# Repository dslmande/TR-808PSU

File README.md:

# TR-808PSU

> ## ⚠️ UNTESTED
>
> **This board has not been manufactured, assembled or tested.** It has not been checked
> against the real unit, and it has not been tested against any safety standard. The design
> is a copy of a historical (1984–86) circuit board. It is connected to **mains voltage
> (230 V, or 110 V for the second variant)**, which can kill. Use at your own risk, and only if you know what you are doing.
> Dimensions are derived from a scan (±3 %), see [VERIFICATION.md](VERIFICATION.md).

KiCad rebuild of the power supply board **PS3116 (PCB 291-405A)** of the Roland TR-808:
schematic redrawn from the 1981 service manual, board with outline, holes, terminals and
component positions taken from the original component layout. Two variants of the same board:

| Variant | Original board | Mains | Transformer | Files |
|---|---|---|---|---|
| **230 V** | PS3116-054 | 220/240 V | N-219D | `TR-808PSU_Rev0.5*` |
| **110 V** | PS3116-051 | 100/117 V (built for 110 V, 117 V tap) | N-218C | `TR-808PSU_Rev0.5-110V*` |

Both use the same copper; they differ in parts (fuses, transformer, switch, C1) and in the
silkscreen mark (`PS3116-054  230V` / `PS3116-051  110V`), so the boards cannot be mixed up.
Current version: **Rev0.5**.

| Version | Contents |
|---|---|
| [Rev0.1](https://github.com/dslmande/TR-808PSU/releases/tag/Rev0.1) | historical 1:1 copy of the 1984–86 original; switched mains conductors SW_A/SW_B 3.75 mm apart |
| [Rev0.2](https://github.com/dslmande/TR-808PSU/releases/tag/Rev0.2) | as Rev0.1, but SW_B moved away on the mains side: SW_A/SW_B at least 5.67 mm apart |
| [Rev0.3](https://github.com/dslmande/TR-808PSU/releases/tag/Rev0.3) | as Rev0.2, but the 230 V primary side (terminals 1–9: mains, switch, transformer input) uses **RM5.0 screw terminals** (Phoenix MKDS 1,5) instead of solder lugs; terminals 10–22 (low voltage) stay solder lugs |
| [Rev0.4](https://github.com/dslmande/TR-808PSU/releases/tag/Rev0.4) / [Rev0.4-110V](https://github.com/dslmande/TR-808PSU/releases/tag/Rev0.4-110V) | as Rev0.3, but all board corners rounded to R5 (house rule), voltage mark on the silkscreen; the 110 V variant is new (fuses 0.5 A, transformer N-218C) |
| **Rev0.5** / **Rev0.5-110V** (current) | as Rev0.4, but the voltage mark moved to the free area below the fuse holders (it touched the F4 outline). Two releases: 230 V and 110 V |

## Pictures (230 V)

### 110 V variant

More (230 V; for 110 V use the `Rev0.5-110V` files, [BOM-110V.md](BOM-110V.md)): [schematic (PDF)](psu/TR-808PSU_Rev0.5_schaltplan.pdf) · [bill of materials](BOM.md) ([CSV](psu/TR-808PSU_Rev0.5_bom.csv)) · [1:1 printout (A4)](psu/TR-808PSU_Rev0.5_ausdruck_1zu1.pdf) · [Gerber (zip)](psu/TR-808PSU_Rev0.5_gerber.zip) · [assembly drawing (PDF)](psu/TR-808PSU_Rev0.5_assembly.pdf) · [original copper vs. tracks](psu/TR-808PSU_Rev0.5_ueberlagerung.png) · [verification](VERIFICATION.md) · [releases](https://github.com/dslmande/TR-808PSU/releases)

## Files

| File | Contents |
|---|---|
| [ORIGINAL.md](ORIGINAL.md) | source, manual pages, variants, circuit description, open points |
| [VERIFICATION.md](VERIFICATION.md) | standards context (DIN EN IEC 62368-1, IEC 60664-1), verification, validation, findings, risks |
| [BOM.md](BOM.md) / [BOM-110V.md](BOM-110V.md), `psu/TR-808PSU_Rev0.5_bom.csv` | bill of materials (readable, with function and original parts; CSV) |
| `psu/TR-808PSU_Rev0.5.kicad_pro` / `.kicad_sch` / `.kicad_pcb` (and `…Rev0.5-110V…`) | KiCad project |
| `psu/TR-808PSU_Rev0.5_schaltplan.pdf` | schematic plot |
| `psu/gerber_TR-808PSU_Rev0.5/`, `psu/TR-808PSU_Rev0.5_gerber.zip` | Gerber, drill data, position file |
| `psu/TR-808PSU_Rev0.5_ausdruck_1zu1.pdf` | 1:1 printout on A4 landscape: component side, solder side, drill template (print at 100 %, check the measuring bar) |
| `psu/TR-808PSU_Rev0.5_3d_oben.png`, `_3d_schraeg.png` | 3D views (KiCad ray tracing; own models for fuse holders and terminal lugs) |
| `psu/TR-808PSU_Rev0.5_pcb_top.pdf`, `_pcb_bottom.pdf`, `_assembly.pdf` | board plots |
| `psu/placement.json`, `psu/placement_scan.json` | component positions from the component layout, resp. aligned to the scan (mm) |
| `psu/kupfer.npz`, `psu/leitkarte.npz` | copper mask and net regions of the original (from the scan) |
| `psu/TR-808PSU_Rev0.5_ueberlagerung.png` | original copper against the tracks of this board |

File names with `schaltplan`, `ausdruck`, `kupfer` and `leitkarte` are German for schematic, printout, copper and guide map.

## What "1:1" means here

* **Circuit:** designators (C1–C16, R1–R7, D1–D4, F1–F4, Q1, Q2, IC1, IC2), values and
  terminal numbers 1–22 as in the original. The schematic is drawn like the original
  (mains and switch left, transformer, +5 V branch, ±15 V branch).
* **Board:** outline (from Rev0.5 with R5 corners instead of the sharp corners of the original), four mounting holes, six heat sink holes (one pair per regulator,
  21.3 mm apart, centred) and three M3 screw holes for the regulators, RM5 screw terminals
  (terminals 1–9), terminal pins (10–22), fuse clips and all components at the positions of
  the original, fine-tuned to the copper of the scan. The original is single
  sided with one wire jumper; this rebuild is two-layer.
* **Tracks: guided by the original, not copied one to one.** The copper of the original is
  extracted from the scan (halftone → mask → net regions) and used as a cost map by the
  router: original copper is cheap, everything else is expensive, the component side is
  almost blocked. The result is a DRC-clean board that follows the original where the scan
  allows. **37 % of the track length lies on original copper**, the rest is routed anew
  (wide tracks and smoothing move the paths away from the original);
  `psu/TR-808PSU_Rev0.5_ueberlagerung.png` shows the original copper (grey) and the tracks
  (red solder side, blue component side). Pure tracing without the router fails because of
  the scan quality (shorts between neighbouring tracks, pad positions only within ±0.3 mm).
* **Dimensions** are derived from the component layout (the manual has no scale), tolerance
  about ±3 %. Measure against a real board before manufacturing. Details and further open
  points in [ORIGINAL.md](ORIGINAL.md).

## Status (Rev0.5, 10 Oct 2026; both variants)

* **ERC:** 0 violations (`psu/TR-808PSU_Rev0.5-erc.rpt`).
* **DRC (clearance rule 0.25 mm):** 0 errors; warnings only (4 courtyard overlaps, 1
  silkscreen overlap, 7 footprint deviations from the library because of the polarity bars);
  0 unconnected items; schematic/board parity 0.
* **Mains against low voltage:** more than 8 mm copper to copper;
  between the mains conductors 4.0–5.67 mm, adjacent terminal poles 2.4 mm (RM5 pitch).
* **Netlist against the schematic:** read by hand from the schematic and checked against the
  plot; no independent comparison, see "Open" in [ORIGINAL.md](ORIGINAL.md).
* Track width 1.0 mm throughout; hairpins and stubs in pads are
  removed; smoothed (45°, arcs). No copper pours, as in the original. Five
  vias; most of the copper is on the solder side, about 440 mm of track on the component side
  (the original used the wire jumper J1 for this).
* **Silkscreen:** designators only (no values), terminal numbers 1–9 next to the screw
  terminals and P10–P22 on the pins, electrolytic polarity as a bar at the minus side as in
  the original, the four fuse holders F1–F4 on one line.
* **Not done:** assembly and measurement on the unit, manufacturing, any safety testing.

## Rebuilding

Schematic and layout were generated with a private tool chain that is not part of this
repo. The KiCad project in `psu/` is complete and needs only KiCad 9/10.

## License

Hardware files (KiCad project, Gerber, schematic, documents):
[CERN-OHL-W-2.0](LICENSE) (CERN Open Hardware Licence v2, weakly reciprocal). The licence
covers only this redrawing and layout, not Roland's original design or manual. Provided as is, without
warranty: see the disclaimer in the licence and the UNTESTED notice above.

## Source and rights

Circuit and dimensions come from the Roland TR-808 service manual (15 June 1981). The manual
itself and the data sheets are not part of this repo (copyright of Roland and the
manufacturers). This repo contains an own redrawing for repair and rebuild. "Roland" and
"TR-808" are trademarks of Roland Corporation; this project is not affiliated with Roland.

Data sheets used to check the pin assignments: 2SB596 (MOSPEC), 2SD880 (DC Components),
TA7179P and µA7805 (service manual, page 2).

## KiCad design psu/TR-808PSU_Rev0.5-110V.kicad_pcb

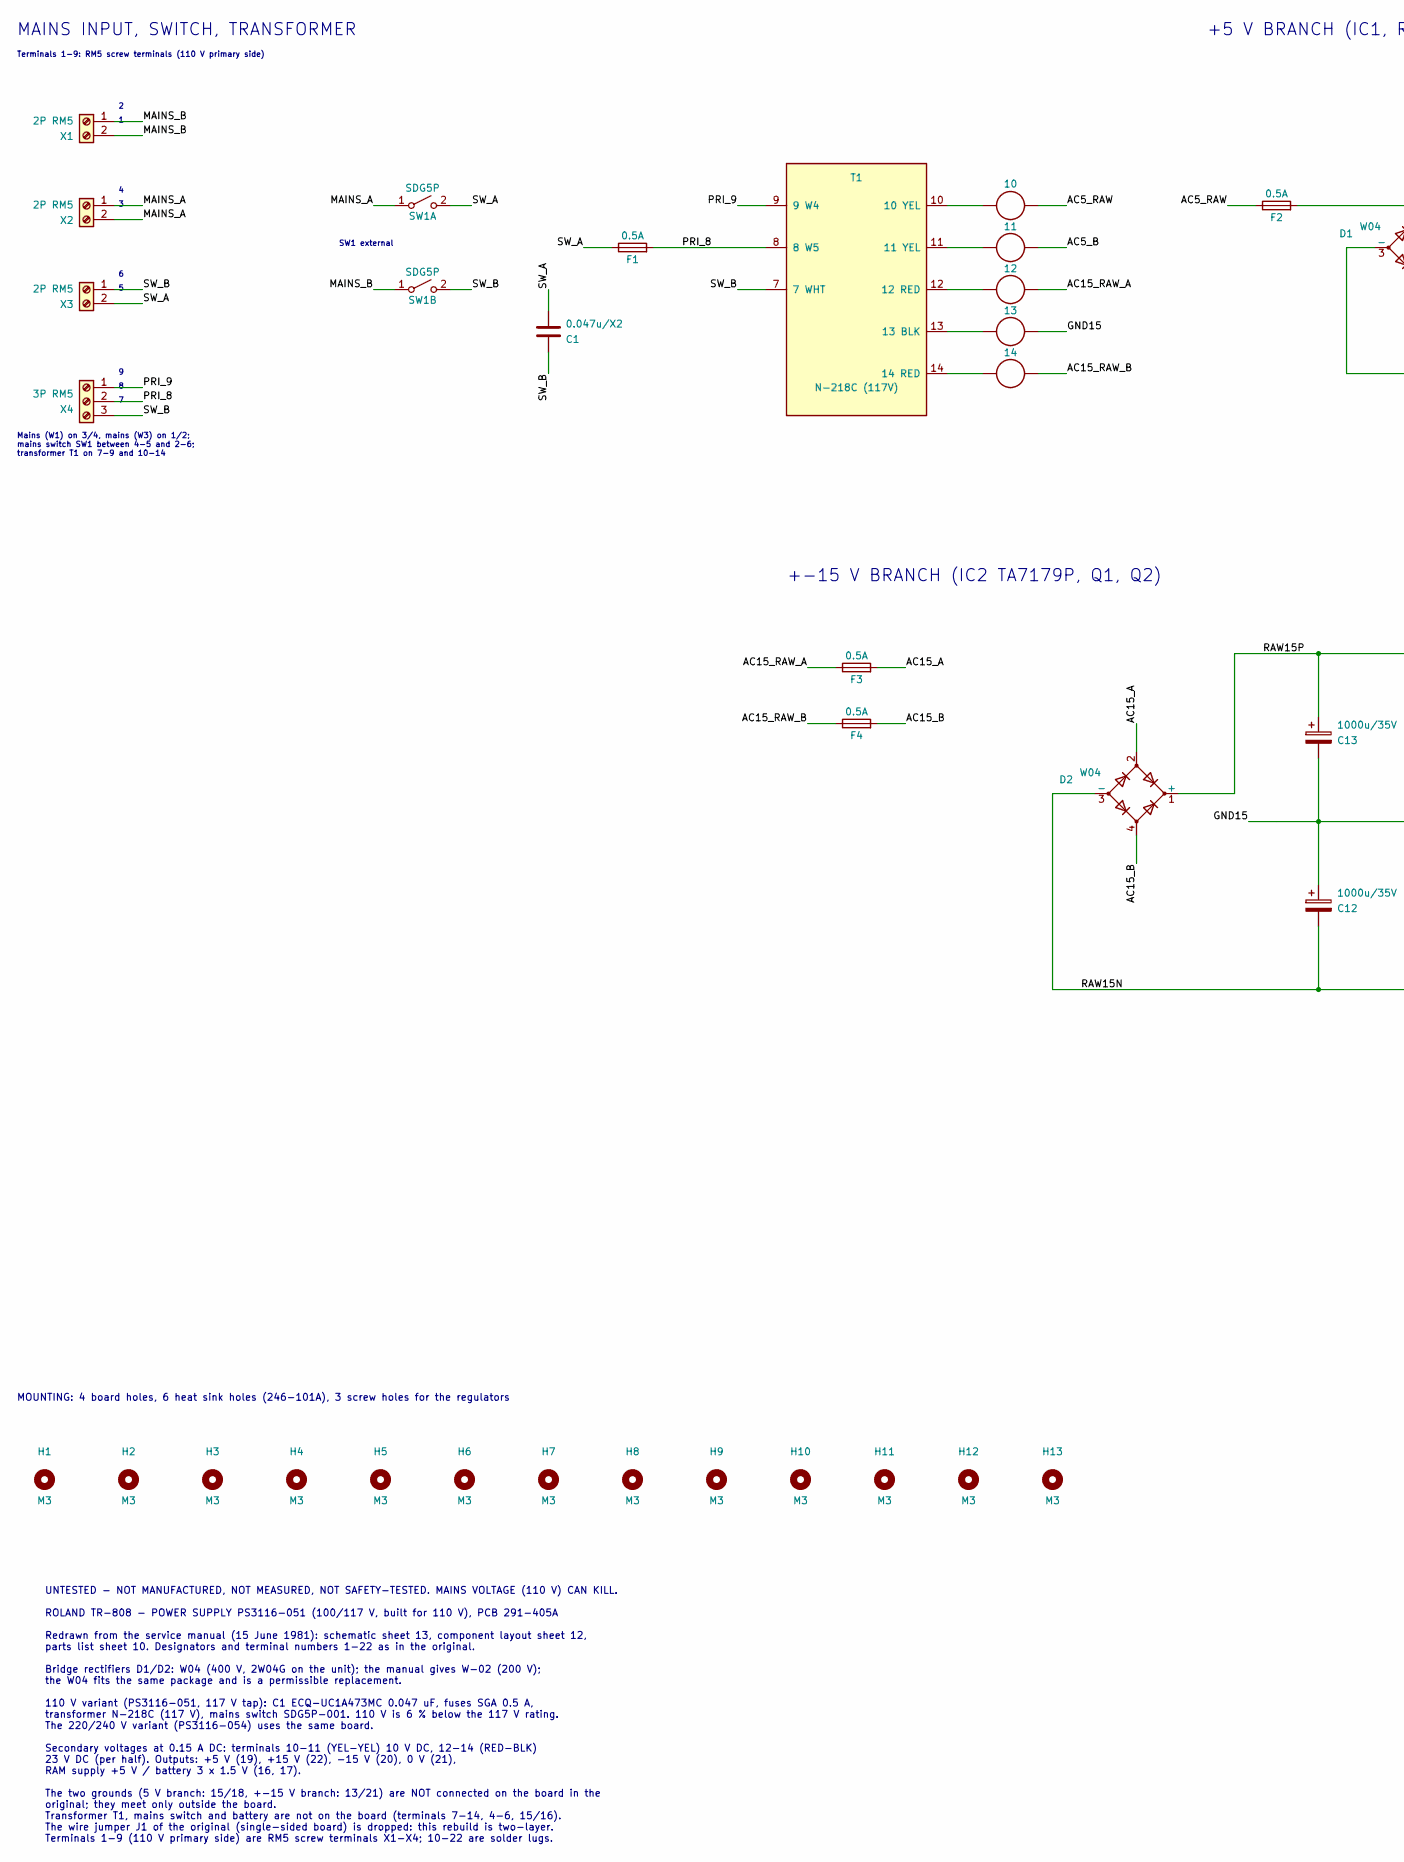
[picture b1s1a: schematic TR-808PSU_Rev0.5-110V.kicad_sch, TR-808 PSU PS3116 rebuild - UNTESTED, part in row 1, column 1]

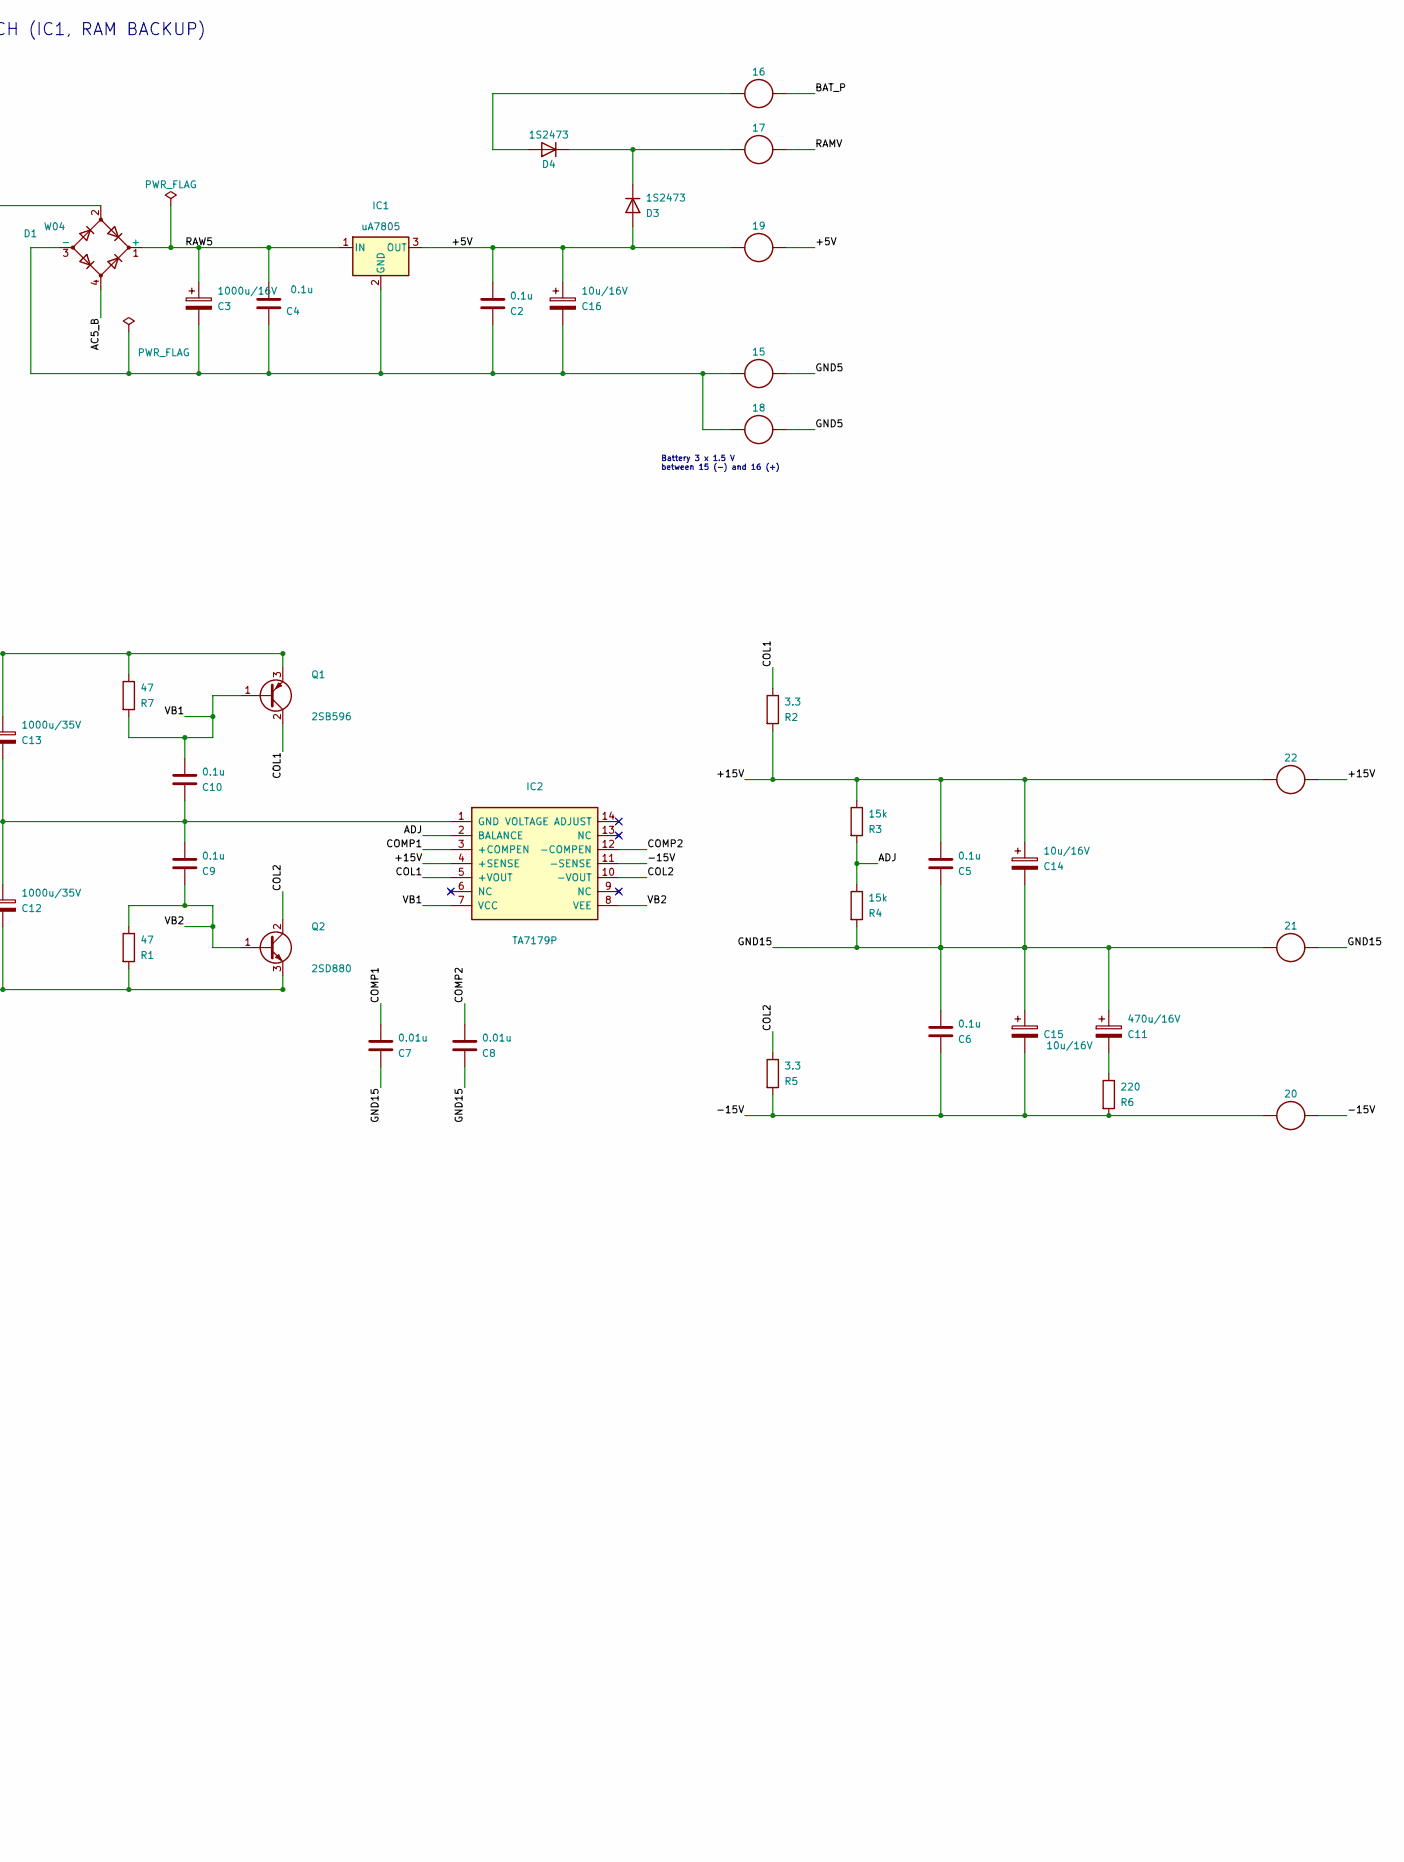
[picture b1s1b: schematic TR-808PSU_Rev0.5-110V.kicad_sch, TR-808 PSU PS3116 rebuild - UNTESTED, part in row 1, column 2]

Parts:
C1: 0.047u/X2; C_Rect_L26.5mm_W8.5mm_P22.50mm_MKS4
C2: 0.1u; C_Rect_L13.0mm_W4.0mm_P10.00mm_FKS3_FKP3_MKS4
C3: 1000u/16V; CP_Radial_D12.5mm_P5.00mm
C4, C5, C6, C9, C10: 0.1u; C_Rect_L10.3mm_W5.0mm_P7.50mm_MKS4
C7: 0.01u; C_Disc_D5.0mm_W2.5mm_P5.00mm
C8: 0.01u; C_Disc_D3.0mm_W2.0mm_P2.50mm
C11: 470u/16V; CP_Radial_D10.0mm_P5.00mm
C12, C13: 1000u/35V; CP_Radial_D16.0mm_P7.50mm
C14, C15, C16: 10u/16V; CP_Radial_D5.0mm_P2.50mm
D1, D2: W04; Diode_Bridge_Round_D9.8mm
D3, D4: 1S2473; D_DO-35_SOD27_P10.16mm_Horizontal
F1, F2, F3, F4: 0.5A; FuseClip_5x20_TF785
H1, H2, H3, H4, H5, H6, H7, H8, H9, H10, H11, H12, H13: M3; MountingHole_3.2mm_M3
IC1: uA7805; TO-220-3_Vertical
IC2: TA7179P; DIP-14_W7.62mm
P10: 10; Terminal_Pin
P11: 11; Terminal_Pin
P12: 12; Terminal_Pin
P13: 13; Terminal_Pin
P14: 14; Terminal_Pin
P15: 15; Terminal_Pin
P16: 16; Terminal_Pin
P17: 17; Terminal_Pin
P18: 18; Terminal_Pin
P19: 19; Terminal_Pin
P20: 20; Terminal_Pin
P21: 21; Terminal_Pin
P22: 22; Terminal_Pin
Q1: 2SB596; TO-220-3_Vertical
Q2: 2SD880; TO-220-3_Vertical
R1: 47; R_Axial_DIN0207_L6.3mm_D2.5mm_P7.62mm_Horizontal
R2, R5: 3.3; R_Axial_DIN0207_L6.3mm_D2.5mm_P10.16mm_Horizontal
R3, R4: 15k; R_Axial_DIN0207_L6.3mm_D2.5mm_P10.16mm_Horizontal
R6: 220; R_Axial_DIN0207_L6.3mm_D2.5mm_P7.62mm_Horizontal
R7: 47; R_Axial_DIN0207_L6.3mm_D2.5mm_P10.16mm_Horizontal
SW1A, SW1B: SDG5P
T1: N-218C (117V)
X1, X2, X3: 2P RM5; TerminalBlock_Phoenix_MKDS-1,5-2_1x02_P5.00mm_Horizontal
X4: 3P RM5; TerminalBlock_Phoenix_MKDS-1,5-3_1x03_P5.00mm_Horizontal

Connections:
/+5V: C2.1, C16.1, D3.2 (A), IC1.3 (OUT), P19.1
/+15V: C5.1, C14.1, IC2.4 (+SENSE), P22.1, R2.2, R3.1
/-15V: C6.2, C15.2, IC2.11 (-SENSE), P20.1, R5.2, R6.2
/AC5_B: D1.4, P11.1, T1.11 (11 YEL)
/AC5_RAW: F2.1, P10.1, T1.10 (10 YEL)
/AC15_A: D2.2, F3.2
/AC15_B: D2.4, F4.2
/AC15_RAW_A: F3.1, P12.1, T1.12 (12 RED)
/AC15_RAW_B: F4.1, P14.1, T1.14 (14 RED)
/ADJ: IC2.2 (BALANCE), R3.2, R4.1
/BAT_P: D4.2 (A), P16.1
/COL1: IC2.5 (+VOUT), Q1.2 (C), R2.1
/COL2: IC2.10 (-VOUT), Q2.2 (C), R5.1
/COMP1: C7.1, IC2.3 (+COMPEN)
/COMP2: C8.1, IC2.12 (-COMPEN)
/GND5: C2.2, C3.2, C4.2, C16.2, D1.3 (-), IC1.2 (GND), P15.1, P18.1
/GND15: C5.2, C6.1, C7.2, C8.2, C9.1, C10.2, C11.1, C12.1, C13.2, C14.2, C15.1, IC2.1 (GND), P13.1, P21.1, R4.2, T1.13 (13 BLK)
/MAINS_A: SW1A.1 (A), X2.1, X2.2
/MAINS_B: SW1B.1 (A), X1.1, X1.2
/PRI_8: F1.2, T1.8 (8 W5), X4.2
/PRI_9: T1.9 (9 W4), X4.1
/RAMV: D3.1 (K), D4.1 (K), P17.1
/RAW5: C3.1, C4.1, D1.1 (+), IC1.1 (IN)
/RAW15N: C12.2, D2.3 (-), Q2.3 (E), R1.2
/RAW15P: C13.1, D2.1 (+), Q1.3 (E), R7.1
/SW_A: C1.1, F1.1, SW1A.2 (B), X3.2
/SW_B: C1.2, SW1B.2 (B), T1.7 (7 WHT), X3.1, X4.3
/VB1: C10.1, IC2.7 (VCC), Q1.1 (B), R7.2
/VB2: C9.2, IC2.8 (VEE), Q2.1 (B), R1.1
unnamed: C11.2, R6.1
unnamed: D1.2, F2.2

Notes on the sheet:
MAINS INPUT, SWITCH, TRANSFORMER
Terminals 1-9: RM5 screw terminals (110 V primary side)
Mains (W1) on 3/4, mains (W3) on 1/2; mains switch SW1 between 4-5 and 2-6; transformer T1 on 7-9 and 10-14
SW1 external
+5 V BRANCH (IC1, RAM BACKUP)
Battery 3 x 1.5 V between 15 (-) and 16 (+)
+-15 V BRANCH (IC2 TA7179P, Q1, Q2)
MOUNTING: 4 board holes, 6 heat sink holes (246-101A), 3 screw holes for the regulators
UNTESTED - NOT MANUFACTURED, NOT MEASURED, NOT SAFETY-TESTED. MAINS VOLTAGE (110 V) CAN KILL. ROLAND TR-808 - POWER SUPPLY PS3116-051 (100/117 V, built for 110 V), PCB 291-405A Redrawn from the service manual (15 June 1981): schematic sheet 13, component layout sheet 12, parts list sheet 10. Design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

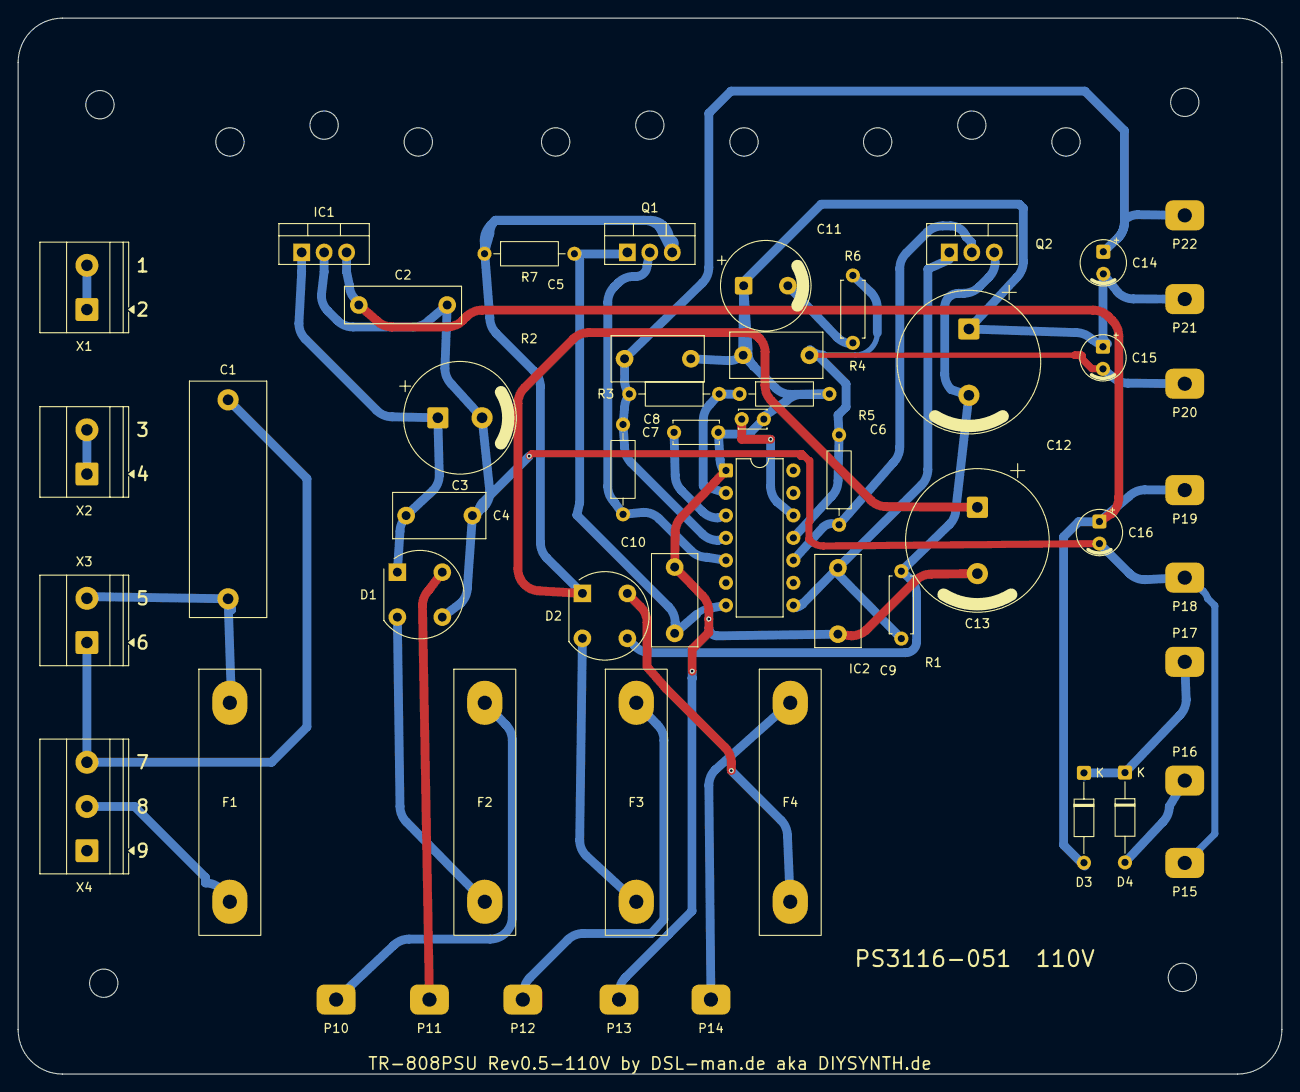
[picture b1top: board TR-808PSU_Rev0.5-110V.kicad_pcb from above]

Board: 2 copper layers, 142.9 x 119.4 mm, 65 parts (0 on the bottom side), 30 nets.
